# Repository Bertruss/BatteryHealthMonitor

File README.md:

## Battery Health Monitor

ATtiny45/85 based dedicated battery health monitor for embedded projects, with small status readout

# Setup Notes:
- lfuse set to 0xE2 to remove the DIV8 and set the clock to full 8mhz

*example: programming using the USBtinyISP via avrdude*
```
avrdude -c usbtiny -p t45 -U lfuse:w:0xE2:m
```
- The font data was intended to be written to eeprom on the chip to save flash, 
not knowing what the total compiled footprint of the code would be beforehand, I assumed I would need to be covetous of the limited 4k flash, and yet as development went on that seemed less and less necessary ¯\\_(ツ)_/¯. 

I used Microchip Studio for a lot of this development. If you want to not clear the eeprom every time you reflash the program storage, set the eeprom protect bit:

```
avrdude -c usbtiny -p t45 -U hfuse:w:0xD7:m
```

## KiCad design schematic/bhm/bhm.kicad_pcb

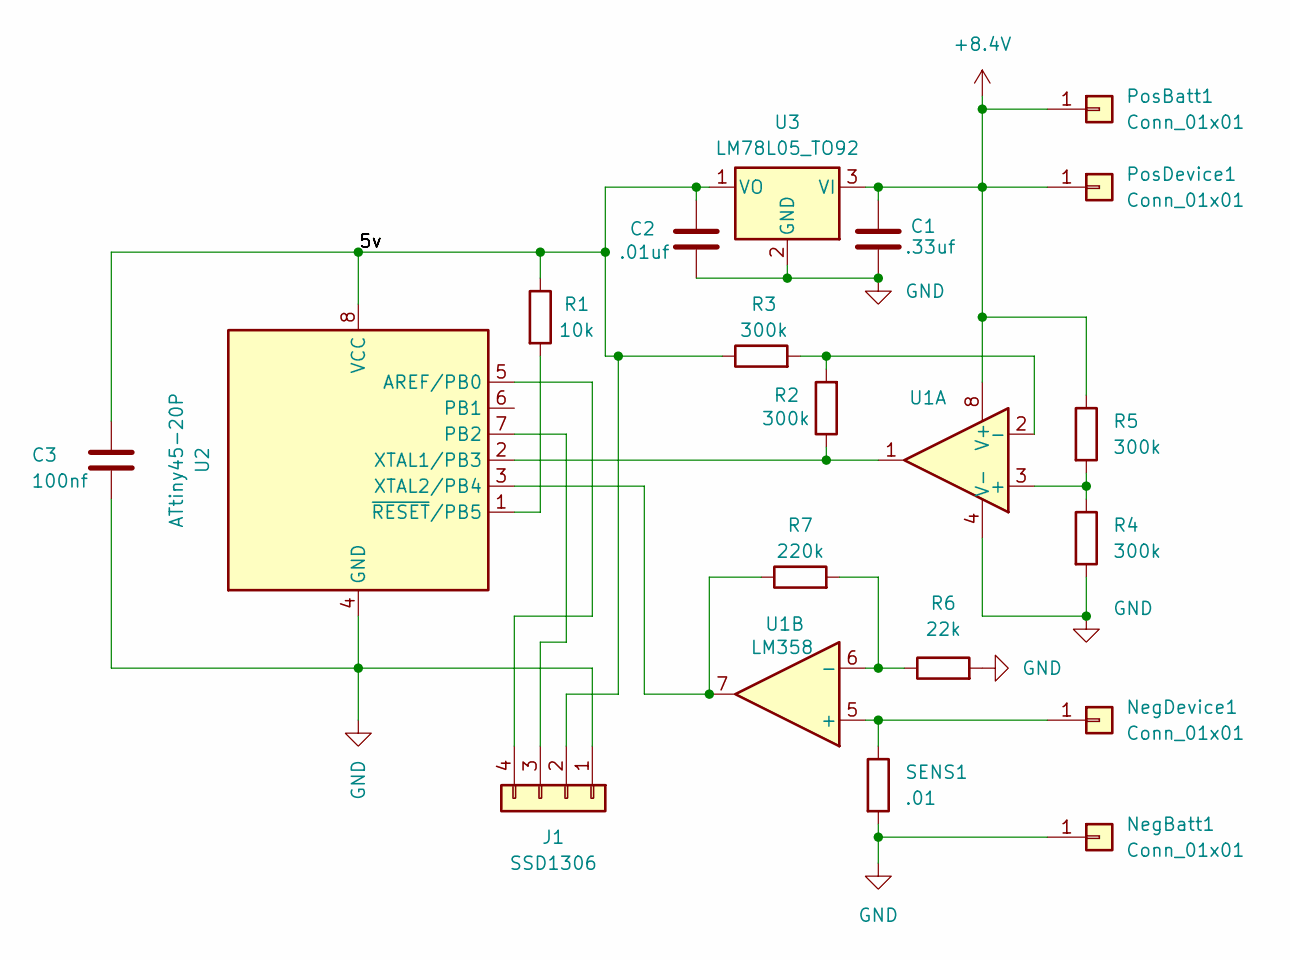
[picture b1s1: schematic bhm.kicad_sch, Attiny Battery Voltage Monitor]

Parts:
C1: .33uf; C_Disc_D3.0mm_W1.6mm_P2.50mm
C2: .01uf; C_Disc_D3.0mm_W1.6mm_P2.50mm
C3: 100nf; C_Radial_D4.0mm_H7.0mm_P1.50mm
J1: SSD1306; PinHeader_1x04_P2.54mm_Vertical
NegBatt1: Conn_01x01; bhm_large_power_pad
NegDevice1: Conn_01x01; bhm_large_power_pad
PosBatt1: Conn_01x01; bhm_large_power_pad
PosDevice1: Conn_01x01; bhm_large_power_pad
R1: 10k; R_Axial_DIN0207_L6.3mm_D2.5mm_P7.62mm_Horizontal
R2, R3, R4, R5: 300k; R_Axial_DIN0207_L6.3mm_D2.5mm_P7.62mm_Horizontal
R6: 22k; R_Axial_DIN0207_L6.3mm_D2.5mm_P7.62mm_Horizontal
R7: 220k; R_Axial_DIN0207_L6.3mm_D2.5mm_P7.62mm_Horizontal
SENS1: .01; R_2816_7142Metric_Pad3.20x4.45mm_HandSolder
U1: LM358; DIP-8_W7.62mm
U2: ATtiny45-20P; DIP-8_W7.62mm
U3: LM78L05_TO92; TO-92_Inline

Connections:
+8.4V: C1.1, PosBatt1.1, PosDevice1.1, R5.1, U1.8 (V+), U3.3 (VI)
/5v: C2.1, C3.1, J1.2, R1.1, R3.1, U2.8 (VCC), U3.1 (VO)
GND: C1.2, C2.2, C3.2, J1.1, NegBatt1.1, R4.2, R6.2, SENS1.2, U1.4 (V-), U2.4 (GND), U3.2 (GND)
unnamed: J1.3, U2.7 (PB2)
unnamed: J1.4, U2.5 (AREF/PB0)
unnamed: NegDevice1.1, SENS1.1, U1.5 (+)
unnamed: R4.1, R5.2, U1.3 (+)
unnamed: R2.2, R3.2, U1.2 (-)
unnamed: R6.1, R7.2, U1.6 (-)
unnamed: R2.1, U1.1, U2.2 (XTAL1/PB3)
unnamed: R7.1, U1.7, U2.3 (XTAL2/PB4)
unnamed: R1.2, U2.1 (~RESET/PB5)

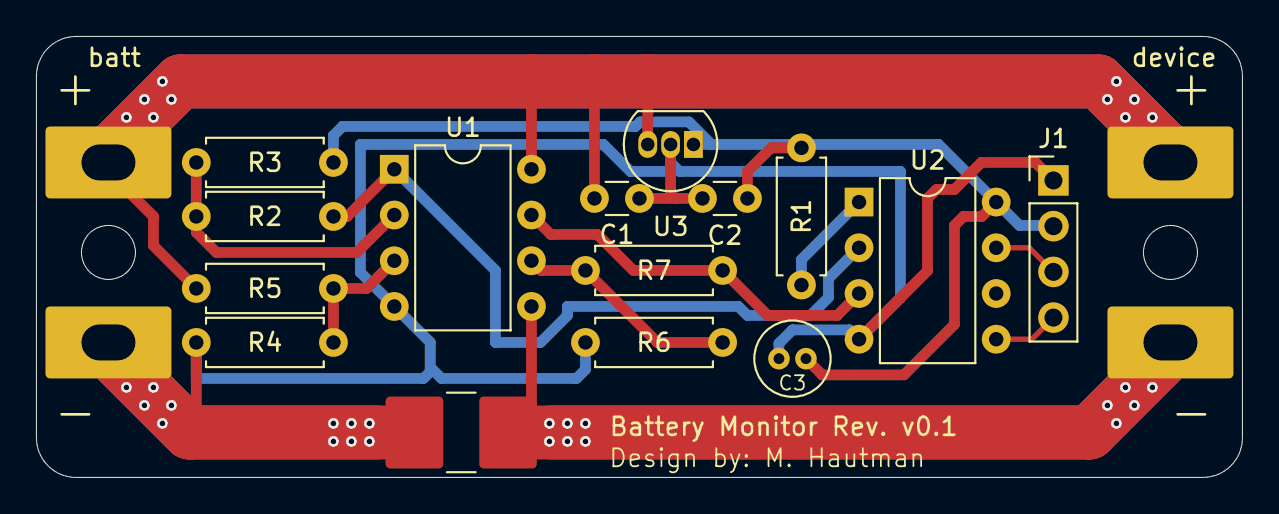
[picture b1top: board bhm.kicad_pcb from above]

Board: 2 copper layers, 67.0 x 24.5 mm, 19 parts (0 on the bottom side), 12 nets.

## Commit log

2024-02-24 init commit
2024-03-05 memory map for eeprom in fnt.h
2024-03-05 implementing small USI I2C
2024-03-05 cleaning up font files
2024-03-05 cleaning up helper scripts
2024-03-06 adding main src file
2024-03-06 WIP i2c implementation. considering not implementing read, out of laziness
2024-03-07 documenting register behavior in the USI, implementing master write logic
2024-03-07 added readme
2024-03-07 whoops wrong extension
2024-03-08 refactoring structure
2024-03-09 Adding start and stop conditions
2024-03-09 Edits too transmission function
2024-03-09 outlining main control loop behaviour
2024-03-09 initializing display driver code. should be pretty minimal
2024-03-10 unless I'm mistaken, transfer code complete
2024-03-10 i2c code is probably done
2024-03-10 Consolidating files out of top level directory
2024-03-11 fixing multiple errors, missing semicolons, etc
2024-03-11 more of the same
2024-03-11 fixing some last inconsistencies
2024-03-14 Major revision after successive debugging
2024-03-14 adding fcpu file to hold F_CPU define to consolidate definition location and to get rid of that annoying warning
2024-03-15 Functioning character writing to screem
2024-03-15 added clarity lines
2024-03-15 Added some more notes to the readme.
2024-03-15 added simple little eeprom routine, integrated into screen lib so that it loads the font data from eeprom
2024-03-16 initiliazing ADC code. I'll admit, I haven't even looked at the documentation yet so maybe this is unnecessary
2024-03-16 functional text display
2024-03-16 Separating some this-project-specific code into it's own display graphics handler.
2024-03-16 adding segment clearing function, rewriting screen clear.
2024-03-16 added 'charlookup' function that returns the eeprom index of the character
2024-03-16 fixing twi bug that sent ack instead of nack to terminate a read mode.
2024-03-20 added various battery health display specific functions
2024-03-20 updating header file
2024-03-23 finishing up functions to write whole screen
2024-03-23 added small 'draw' function to screen.
2024-03-23 miscounted :[
2024-03-25 honestly don't remember
2024-03-25 outlining ADC usage
2024-03-25 testing
2024-03-25 Round of debugging. fixed value -> address conversion in several. fixed compilation issues.
2024-03-25 debugging, fixed compile time issues
2024-03-26 I made a new branch for this but that may have been unnecessary. this is fairly simple
2024-03-26 added file to store moderately high resolution scaling parameters
2024-03-26 merging main into adc
2024-03-26 added some compile guards
2024-03-27 initial commit of circuit design. using KiCAD.
2024-03-27 making sure includes use accurate paths
2024-03-27 small fixes
2024-03-27 updating display_voltage to use proper scaling
2024-03-28 adding KiCad schematic
2024-04-02 breaking constants into source and header. I believe I was using 'extern' wrong
2024-04-02 rewriting constants for legibility
2024-04-04 display_voltage rework
2024-04-04 reworked to use differential opamp
2024-04-04 removed some errant code
2024-04-04 reworking main function to be closer to planned solution
2024-04-04 consolidating bhm specific sources to more generic lib folder
2024-04-04 consolidating bhm specific sources to more generic lib folder. creating specific Utils files. copying over ADCscale files which are really specific to this use case.
2024-04-04 added some documentation to the helper scripts
2024-04-05 added small SPICE sim to check values
2024-04-05 updating schematic with footprints also fixing terrible layout
2024-04-05 explaining use of helper scripts and how to flash the font
2024-04-05 implemented functions to measure battery voltage with vcc compensation
2024-04-06 removed some innaccurate comments from the main source file.
2024-04-11 there's no power operator in c -_-
2024-04-11 fixing conversion from uint to decimal num
2024-04-11 Fixing adc conversion, adding back reference voltage which is accurate to the function of the bhm circuitry
2024-04-11 switching off reference voltage after measurement
2024-04-11 slight rework, update_display for voltage from 16 to 32 bit
2024-04-11 voltage from 16 to 32 bits
2024-04-11 bug-fixing, updating data-types and removing unused variables
2024-04-22 adjusting screen brightness, adding brightness control
2024-04-25 added initial brightness setting
2024-04-25 adding adc sleep-read
2024-04-25 fixing some bugs
2024-04-25 making the adc read use the sleep/low-noise functionality
2024-04-25 testing gain settings with expected current sensing configuration
2024-04-25 testing out generating some preliminary pcb layouts
2024-05-07 outlining v1 program cycle
2024-05-07 Adding flexibility to adc input selection
2024-05-07 assuming all lipos work this way... added cell number configuration parameter
2024-05-08 flashing out ADC changes to utilization stages
2024-05-08 adjustments to schematic
2024-05-08 interrupt test
2024-05-08 added blurb to screen driver code
2024-05-08 fixing numerous syntax errors
2024-05-08 fixing syntax errors
2024-05-25 multiple changes to reduce size. tracking down bug with ADC.
2024-06-05 added enable/disable to TWI
2024-06-05 removing explicit function for disabling the digital input buffer. seems that any analog read pin would only need to do this once, so it should be configured in a setup function.
2024-06-05 adding some test functions for reading the output of the ADC.
2024-06-05 using averaging to stabilize ADC jitter
2024-06-05 untracking some unintentionally tracked dev files
2024-06-18 fixing sleep cycles
2024-06-24 Added power throughhole solder points. reorg'd schematic for low side current measurement
2024-07-04 refactoring file structure manual Makefile build process
2024-07-07 refactoring include references for proper relative path. able to do this without the relative references?
2025-01-18 resurrecting this project to finish it. for some reason, something changed and now I have about half the flash left after compiling.
2025-01-18 fixing some incorrect relative paths for include statements
2025-01-26 adding example fuse flash to README just so I don't forget how next time
2025-01-26 renaming ADCscale to reflect the fact the values therein are specific to the BHM use case. this is preemptive to expanding the constants declared here.
2025-02-04 fixing some refactoring issues
2025-03-07 added macro identifying the start of the numeric characters in the character bitmap lookup table
2025-03-07 added several useful defines. 1e8 fixed point. look up table to map voltages to charge estimate.
2025-03-07 genericized 3 digit num display. added current readout
2025-03-07 added current draw measurement, added multi-modal charge estimation
2025-03-07 implementation
2025-03-07 added line to set data direction register DDRB to all input...
2025-03-12 adding constant describing the number of amps corresponding to volts sensed at the ADC pin
2025-03-12 Due to the fact current measurements will need to be much higher in range than voltage measurements, added optional extra digit
2025-03-12 potentially fixing math for calculating measured current. might still be wrong, idk
2025-03-16 refactoring adc usage for size, changing fixed point to be a binary rather than decimal value.
2025-03-30 changed constant vars to Const, which I didn't think was necessary
2025-03-30 added single character delete function, which might be superfluous but whatever
2025-03-30 ditto of last commit
2025-03-30 WIP testing commit
2025-04-06 fixing cursor character delete code
2025-04-06 adding some utility defines
2025-04-06 clarifying some comments
2025-04-06 WIP adding math utils to approximate nonlinear charge/voltage relationship instead of using lookuptable, though the current lut was used to derive the function. function will be included in future co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
2025-04-06 small sim for prototyping circuit
2025-04-06 updating schematic values
2025-04-06 logic testing for charge estimation.
2025-04-26 added ms time tracker using timer/counter1
2025-04-26 added utilities for fixed point exp, power, log2, ln, abs
2025-04-26 removed lookuptable. switching to nonlinear approximation based on best fit to the lookuptables data.
2025-04-26 a few modifications. restructed to use more generic function calls for writing the voltage and current. fixed the final lines of the percent bar so that theres a gap. added a bit of testing code that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
2025-04-26 WIP, added nonlinear approximation of battery charge based on battery voltage, switching from LUT. unfortunately, the math required took up the rest of the Attiny45's ram, and thus I decided to branc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
2025-04-26 had not kept consistent with defining table sizes for screen instruction templates
2025-04-26 removed a lot of unnecessary calls to the sreg to pause and enable interrupts.
2025-04-26 math logic scatchpad
2025-04-26 using 'const' to save memory
2025-04-26 accidently put hfuse instead of lfuse
2025-05-07 finalized v1 schematic and PCB layout
2026-02-11 checkpoint: debugging hang at 100 percent charge calculation
2026-05-05 unfortunately, giving up on the sigmoid charge/voltage approximation, implemented piecewise function. Exponents were simply too large. It was, maybe a more elegant solution (?) but the piecewise cubi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
2026-05-05 clean up
